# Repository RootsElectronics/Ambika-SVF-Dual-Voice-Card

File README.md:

# Ambika-SVF-Dual-Voice-Card
Adaptation of the Mutable Instruments Ambika SVF Voice Card in 0603 SMD, with 2 Voices per voice card

My initial prototype (verified working at 02/2021) utilised the original through hole zener diodes. On this version I have simply changed those for a surface mount equivalent. 

Will upload BOM soon, but for now:

There are a few of these out in the wild now, someone kindly noted a fix for calibration they were having on 2 out of their 3 voice cards.

To quote

"I swapped R10 and R32 to 36k and they all calibrated approximately in the middle of the range (it may be worth experimenting with the feedback cap as well I guess.... but I'm not going to !)"

Original design by émilie gillet

CC-BY-SA 3.0

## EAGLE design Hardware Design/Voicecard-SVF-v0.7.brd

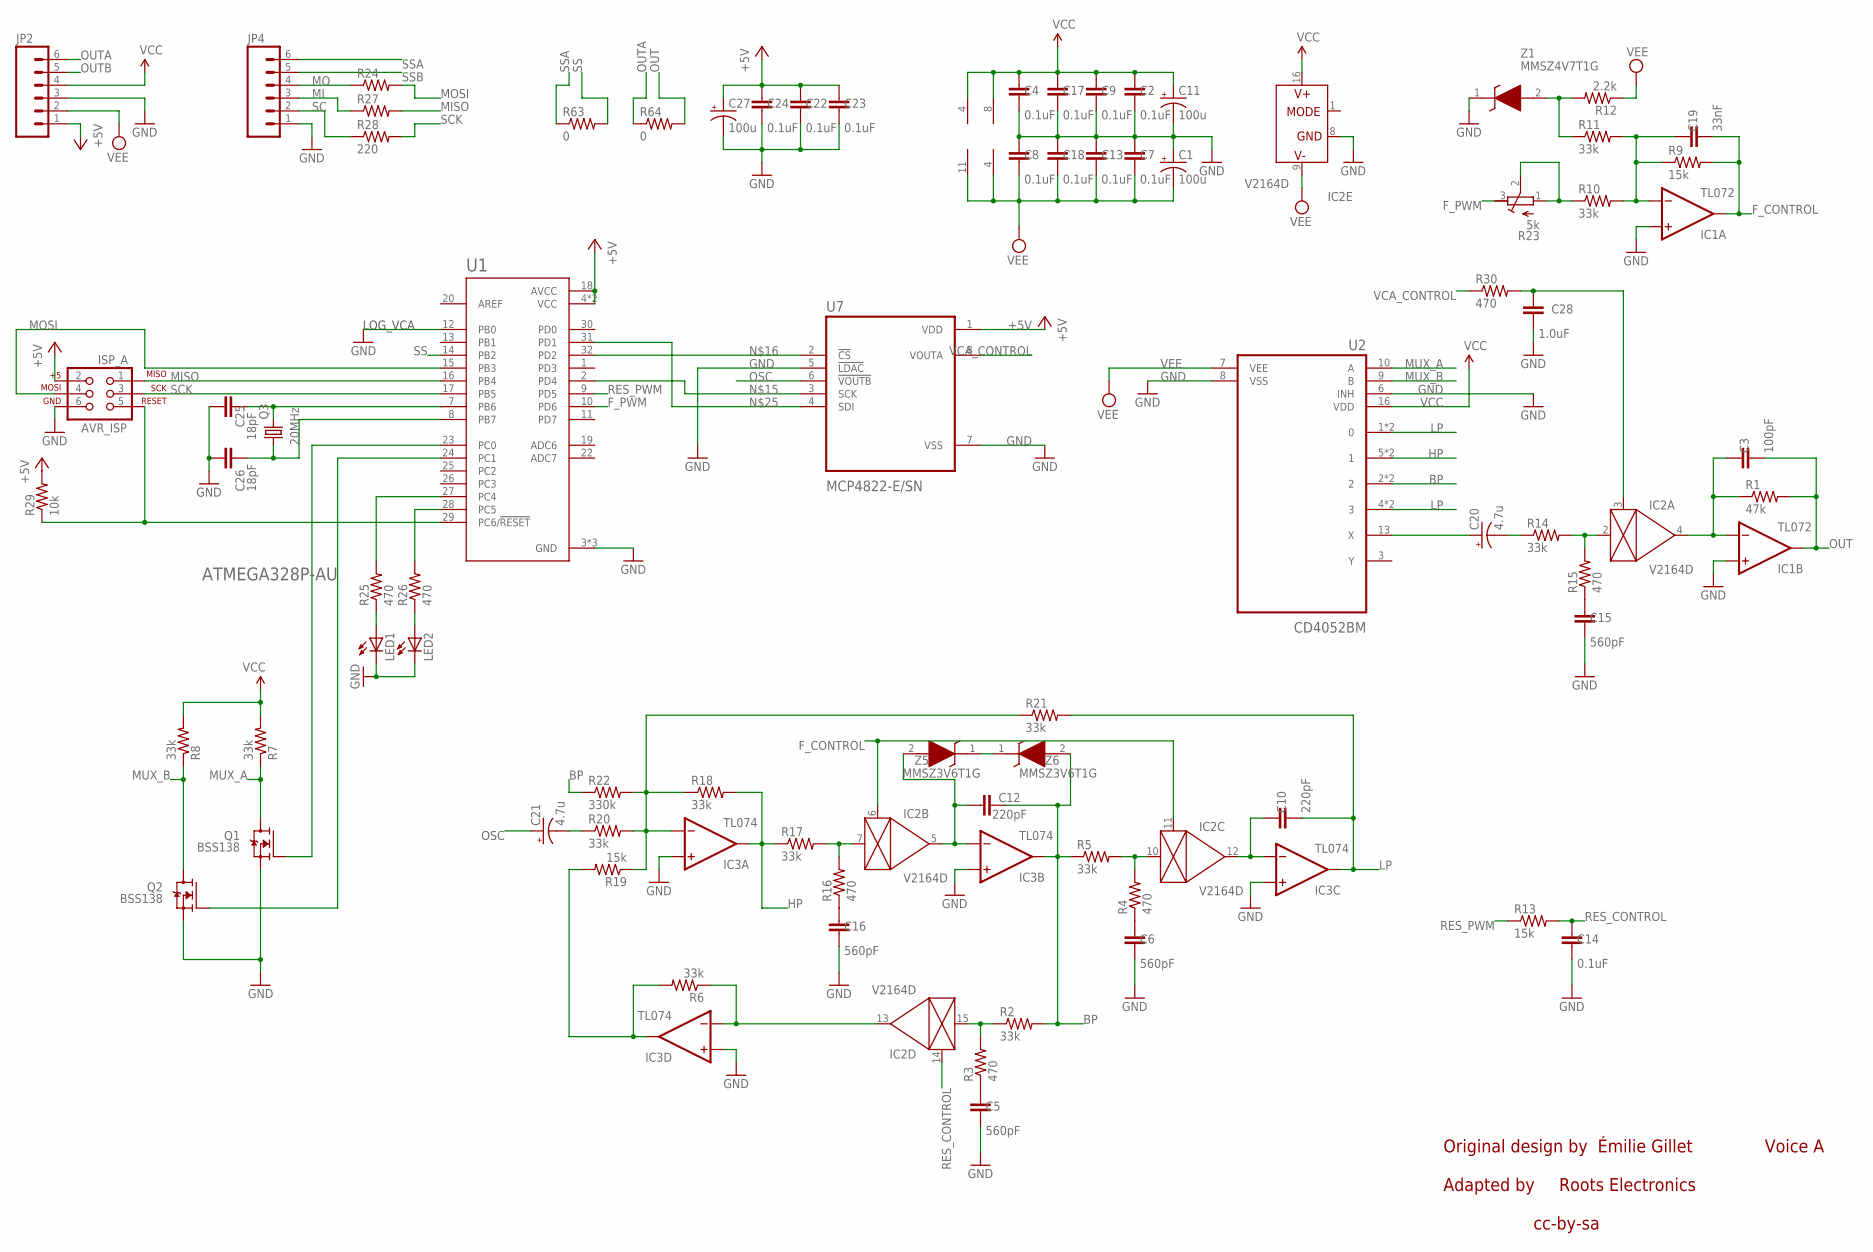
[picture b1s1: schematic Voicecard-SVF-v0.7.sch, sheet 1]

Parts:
C1, C11, C27: 100u; PANASONIC_C
C2, C4, C7, C8, C9, C13, C14, C17, C18, C22, C23, C24: 0.1uF; 0603
C3: 100pF; 0603
C5, C6, C15, C16: 560pF; 0603
C10, C12: 220pF; 0603
C19: 33nF; 0603
C20, C21: 4.7u; PANASONIC_A
C25, C26: 18pF; 0603
C28: 1.0uF; 0603
IC1: TL072; SO08
IC2: V2164D; SOIC16N
IC3: TL074; SO14
ISP_A: AVR_ISP; 2X3
JP2, JP4: M06SIP; 1X06
LED1, LED2: LED3MM
Q1, Q2: BSS138; SOT95P240X111-3N
Q3: 20MHz; HC49UP
R1: 47k; 0603
R2, R5, R6, R7, R8, R10, R11, R14, R17, R18, R20, R21: 33k; 0603
R3, R4, R15, R16, R25, R26, R30: 470; 0603
R9, R13, R19: 15k; 0603
R12: 2.2k; 0603
R22: 330k; 0603
R23: 5k; RTRIM3296P
R24, R27, R28: 220; 0603
R29: 10k; 0603
R63, R64: 0; 0603
U1: ATMEGA328P-AU; QFP80P900X900X120-32N
U2: CD4052BM; SOIC127P600X175-16N
U7: MCP4822-E/SN; SOIC127P599X175-8N
Z1: MMSZ4V7T1G; SOD3716X135N
Z5, Z6: MMSZ3V6T1G; SOD3716X135N

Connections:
+5V: C22.1, C23.1, C24.1, C27.+, ISP_A.2, JP2.1, R29.2, U1.4 (VCC), U1.6 (VCC), U1.18 (AVCC), U7.1 (VDD); also elsewhere on the board
BP: C12.2, IC3.7 (OUT), R2.2, R5.1, R22.1, U2.2, U2.15 (2), Z6.2 (A)
F_CONTROL: C19.2, IC1.1 (OUT), IC2.6 (CTRL), IC2.11 (CTRL), R9.2
F_PWM: R23.3 (A), U1.10 (PD6)
GND: C1.+, C2.2, C4.2, C5.2, C6.2, C7.1, C8.1, C9.2, C11.-, C13.1, C14.2, C15.2, C16.2, C17.2, C18.1, C22.2, C23.2, C24.2, C25.1, C26.1, C27.-, C28.2, IC1.3 (+IN), IC1.5 (+IN), IC2.8 (GND), IC3.3 (+IN), IC3.5 (+IN), IC3.10 (+IN), IC3.12 (+IN), ISP_A.6, JP2.3, JP4.1, LED1.K (C), LED2.K (C), Q1.2 (S), Q2.2 (S), U1.3 (GND), U1.5 (GND), U1.12 (PB0), U1.21 (GND), U2.6 (INH), U2.8 (VSS), U7.5 (!LDAC), U7.7 (VSS), Z1.1 (K); also elsewhere on the board
HP: IC3.1 (OUT), R17.1, R18.2, U2.5 (1), U2.14 (1)
LEDS0: R25.2, U1.27 (PC4)
LP: C10.2, IC3.8 (OUT), R21.2, U2.1 (0), U2.4 (3), U2.11 (3), U2.12 (0)
MI: JP4.3, R27.1; also elsewhere on the board
MISO: ISP_A.1, R27.2, U1.16 (PB4)
MO: JP4.4, R24.1; also elsewhere on the board
MOSI: ISP_A.4, R24.2, U1.15 (PB3)
MUX_A: Q1.3 (D), R7.1, U2.10 (A)
MUX_B: Q2.3 (D), R8.1, U2.9 (B)
unnamed: C21.-, R20.1
unnamed: C20.+, U2.13 (X)
unnamed: Q1.1 (G), U1.23 (PC0)
unnamed: C20.-, R14.1
unnamed: Q2.1 (G), U1.24 (PC1)
unnamed: LED1.A, R25.1
unnamed: R11.1, R12.2, Z1.2 (A)
unnamed: LED2.A, R26.1
unnamed: R26.2, U1.28 (PC5)
unnamed: IC3.2 (-IN), R18.1, R19.1, R20.2, R21.1, R22.2
unnamed: U1.2 (PD4), U7.3 (SCK)
unnamed: U1.32 (PD2), U7.2 (!CS)
unnamed: C6.1, R4.1
unnamed: C12.1, IC2.5 (OUT), IC3.6 (-IN), Z5.2 (A)
unnamed: IC2.15 (IN), R2.1, R3.2
unnamed: ISP_A.5, R29.1, U1.29 (PC6/!RESET)
unnamed: U1.31 (PD1), U7.4 (SDI)
unnamed: IC2.10 (IN), R4.2, R5.2
unnamed: C5.1, R3.1
unnamed: C10.1, IC2.12 (OUT), IC3.9 (-IN)
unnamed: IC2.7 (IN), R16.2, R17.2
unnamed: C16.1, R16.1
unnamed: IC2.13 (OUT), IC3.13 (-IN), R6.1
unnamed: C19.1, IC1.2 (-IN), R9.1, R10.2, R11.2
unnamed: R10.1, R23.1 (E), R23.2 (S)
unnamed: IC3.14 (OUT), R6.2, R19.2
unnamed: Z5.1 (K), Z6.1 (K)
unnamed: C15.1, R15.1
unnamed: IC2.2 (IN), R14.2, R15.2
unnamed: C3.1, IC1.6 (-IN), IC2.4 (OUT), R1.1
unnamed: C26.2, Q3.1, U1.8 (PB7)
unnamed: C25.2, Q3.2, U1.7 (PB6)
NET55: C28.1, IC2.3 (CTRL), R30.2
OSC: C21.+, U7.6 (!VOUTB)
OUT: C3.2, IC1.7 (OUT), R1.2, R64.2
OUTA: JP2.6, R64.1
OUTB: JP2.5; also elsewhere on the board
RES_CONTROL: C14.1, IC2.14 (CTRL), R13.2
RES_PWM: R13.1, U1.9 (PD5)
SC: JP4.2, R28.1; also elsewhere on the board
SCK: ISP_A.3, R28.2, U1.17 (PB5)
SS: R63.2, U1.14 (PB2)
SSA: JP4.6, R63.1
SSB: JP4.5; also elsewhere on the board
VCA_CONTROL: R30.1, U7.8 (VOUTA)
VCC: C2.1, C4.1, C9.1, C11.+, C17.1, IC1.8 (V+), IC2.16 (V+), IC3.4 (V+), JP2.4, R7.2, R8.2, U2.16 (VDD); also elsewhere on the board
VEE: C1.-, C7.2, C8.2, C13.2, C18.2, IC1.4 (V-), IC2.9 (V-), IC3.11 (V-), JP2.2, R12.1, U2.7 (VEE); also elsewhere on the board

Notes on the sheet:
Original design by
Émilie Gillet
LOG_VCA
Voice A
cc-by-sa
Adapted by
Roots Electronics

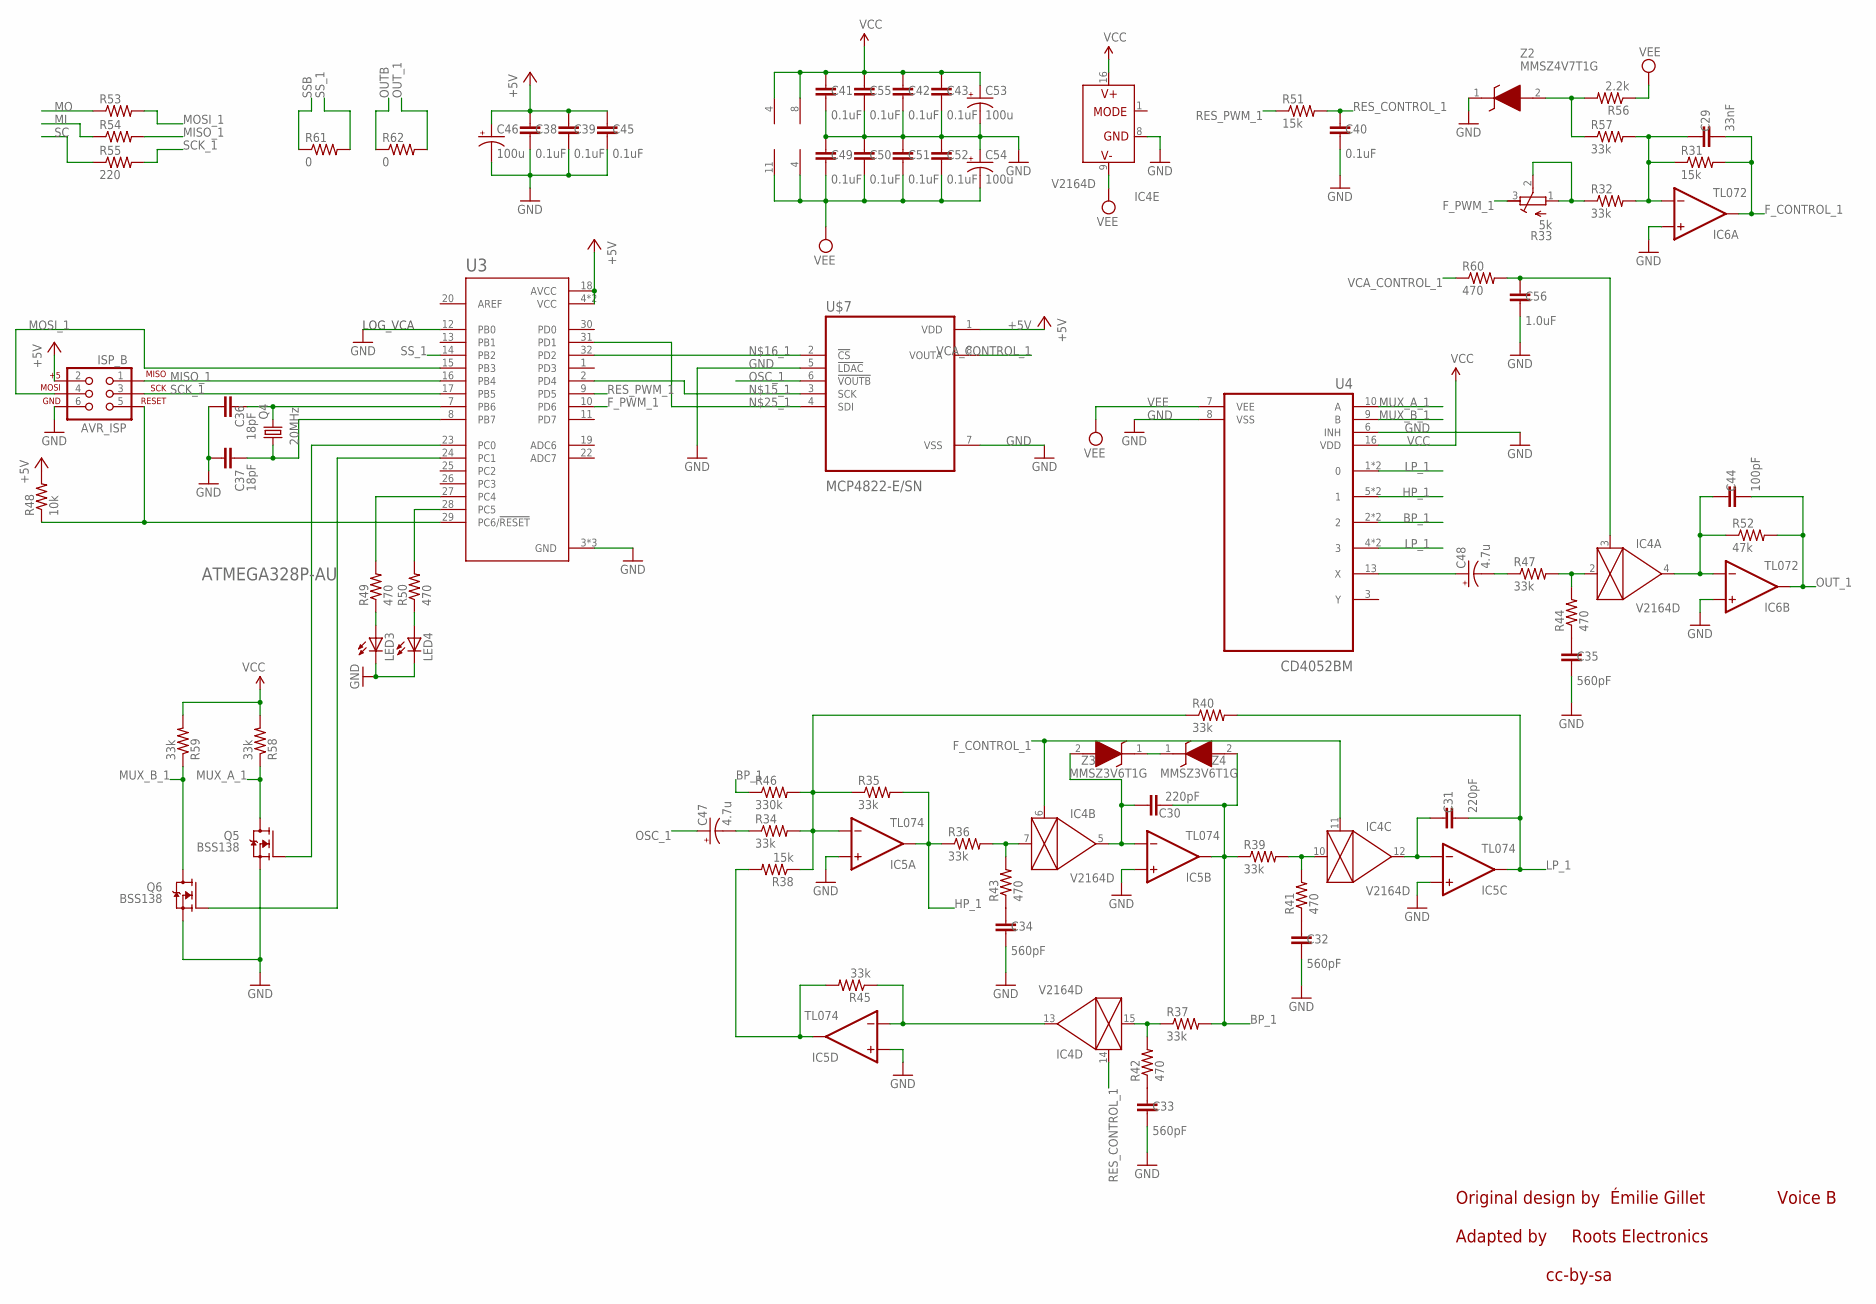
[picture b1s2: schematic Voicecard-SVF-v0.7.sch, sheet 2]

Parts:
C29: 33nF; 0603
C30, C31: 220pF; 0603
C32, C33, C34, C35: 560pF; 0603
C36, C37: 18pF; 0603
C38, C39, C40, C41, C42, C43, C45, C49, C50, C51, C52, C55: 0.1uF; 0603
C44: 100pF; 0603
C46, C53, C54: 100u; PANASONIC_C
C47, C48: 4.7u; PANASONIC_A
C56: 1.0uF; 0603
IC4: V2164D; SOIC16N
IC5: TL074; SO14
IC6: TL072; SO08
ISP_B: AVR_ISP; 2X3
LED3, LED4: LED3MM
Q4: 20MHz; HC49UP
Q5, Q6: BSS138; SOT95P240X111-3N
R31, R38, R51: 15k; 0603
R32, R34, R35, R36, R37, R39, R40, R45, R47, R57, R58, R59: 33k; 0603
R33: 5k; RTRIM3296P
R41, R42, R43, R44, R49, R50, R60: 470; 0603
R46: 330k; 0603
R48: 10k; 0603
R52: 47k; 0603
R53, R54, R55: 220; 0603
R56: 2.2k; 0603
R61, R62: 0; 0603
U3: ATMEGA328P-AU; QFP80P900X900X120-32N
U4: CD4052BM; SOIC127P600X175-16N
U$7: MCP4822-E/SN; SOIC127P599X175-8N
Z2: MMSZ4V7T1G; SOD3716X135N
Z3, Z4: MMSZ3V6T1G; SOD3716X135N

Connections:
+5V: C38.1, C39.1, C45.1, C46.+, ISP_B.2, R48.2, U3.4 (VCC), U3.6 (VCC), U3.18 (AVCC), U$7.1 (VDD); also elsewhere on the board
BP_1: C30.2, IC5.7 (OUT), R37.2, R39.1, R46.1, U4.2, U4.15 (2), Z4.2 (A)
F_CONTROL_1: C29.2, IC4.6 (CTRL), IC4.11 (CTRL), IC6.1 (OUT), R31.2
F_PWM_1: R33.3 (A), U3.10 (PD6)
GND: C32.2, C33.2, C34.2, C35.2, C36.1, C37.1, C38.2, C39.2, C40.2, C41.2, C42.2, C43.2, C45.2, C46.-, C49.1, C50.1, C51.1, C52.1, C53.-, C54.+, C55.2, C56.2, IC4.8 (GND), IC5.3 (+IN), IC5.5 (+IN), IC5.10 (+IN), IC5.12 (+IN), IC6.3 (+IN), IC6.5 (+IN), ISP_B.6, LED3.K (C), LED4.K (C), Q5.2 (S), Q6.2 (S), U3.3 (GND), U3.5 (GND), U3.12 (PB0), U3.21 (GND), U4.6 (INH), U4.8 (VSS), U$7.5 (!LDAC), U$7.7 (VSS), Z2.1 (K); also elsewhere on the board
HP_1: IC5.1 (OUT), R35.2, R36.1, U4.5 (1), U4.14 (1)
LEDS1_1: R49.2, U3.27 (PC4)
LP_1: C31.2, IC5.8 (OUT), R40.2, U4.1 (0), U4.4 (3), U4.11 (3), U4.12 (0)
MI: R54.1; also elsewhere on the board
MISO_1: ISP_B.1, R54.2, U3.16 (PB4)
MO: R53.1; also elsewhere on the board
MOSI_1: ISP_B.4, R53.2, U3.15 (PB3)
MUX_A_1: Q5.3 (D), R58.1, U4.10 (A)
MUX_B_1: Q6.3 (D), R59.1, U4.9 (B)
unnamed: C29.1, IC6.2 (-IN), R31.1, R32.2, R57.2
unnamed: R32.1, R33.1 (E), R33.2 (S)
unnamed: C44.1, IC4.4 (OUT), IC6.6 (-IN), R52.1
unnamed: IC5.2 (-IN), R34.2, R35.1, R38.1, R40.1, R46.2
unnamed: U3.2 (PD4), U$7.3 (SCK)
unnamed: U3.32 (PD2), U$7.2 (!CS)
unnamed: C30.1, IC4.5 (OUT), IC5.6 (-IN), Z3.2 (A)
unnamed: IC4.10 (IN), R39.2, R41.2
unnamed: C31.1, IC4.12 (OUT), IC5.9 (-IN)
unnamed: C32.1, R41.1
unnamed: U3.31 (PD1), U$7.4 (SDI)
unnamed: C33.1, R42.1
unnamed: IC4.7 (IN), R36.2, R43.2
unnamed: C34.1, R43.1
unnamed: C35.1, R44.1
unnamed: IC4.2 (IN), R44.2, R47.2
unnamed: IC4.15 (IN), R37.1, R42.2
unnamed: IC4.13 (OUT), IC5.13 (-IN), R45.1
unnamed: IC5.14 (OUT), R38.2, R45.2
unnamed: Z3.1 (K), Z4.1 (K)
unnamed: C47.-, R34.1
unnamed: C48.-, R47.1
unnamed: C37.2, Q4.1, U3.8 (PB7)
unnamed: C36.2, Q4.2, U3.7 (PB6)
unnamed: LED3.A, R49.1
unnamed: LED4.A, R50.1
unnamed: R50.2, U3.28 (PC5)
unnamed: R56.2, R57.1, Z2.2 (A)
unnamed: ISP_B.5, R48.1, U3.29 (PC6/!RESET)
unnamed: Q5.1 (G), U3.23 (PC0)
unnamed: Q6.1 (G), U3.24 (PC1)
unnamed: C48.+, U4.13 (X)
NET1: C56.1, IC4.3 (CTRL), R60.2
OSC_1: C47.+, U$7.6 (!VOUTB)
OUTB: R62.1; also elsewhere on the board
OUT_1: C44.2, IC6.7 (OUT), R52.2, R62.2
RES_CONTROL_1: C40.1, IC4.14 (CTRL), R51.2
RES_PWM_1: R51.1, U3.9 (PD5)
SC: R55.1; also elsewhere on the board
SCK_1: ISP_B.3, R55.2, U3.17 (PB5)
SSB: R61.1; also elsewhere on the board
SS_1: R61.2, U3.14 (PB2)
VCA_CONTROL_1: R60.1, U$7.8 (VOUTA)
VCC: C41.1, C42.1, C43.1, C53.+, C55.1, IC4.16 (V+), IC5.4 (V+), IC6.8 (V+), R58.2, R59.2, U4.16 (VDD); also elsewhere on the board
VEE: C49.2, C50.2, C51.2, C52.2, C54.-, IC4.9 (V-), IC5.11 (V-), IC6.4 (V-), R56.1, U4.7 (VEE); also elsewhere on the board

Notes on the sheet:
LOG_VCA
Voice B
Original design by
Émilie Gillet
cc-by-sa
Adapted by
Roots Electronics

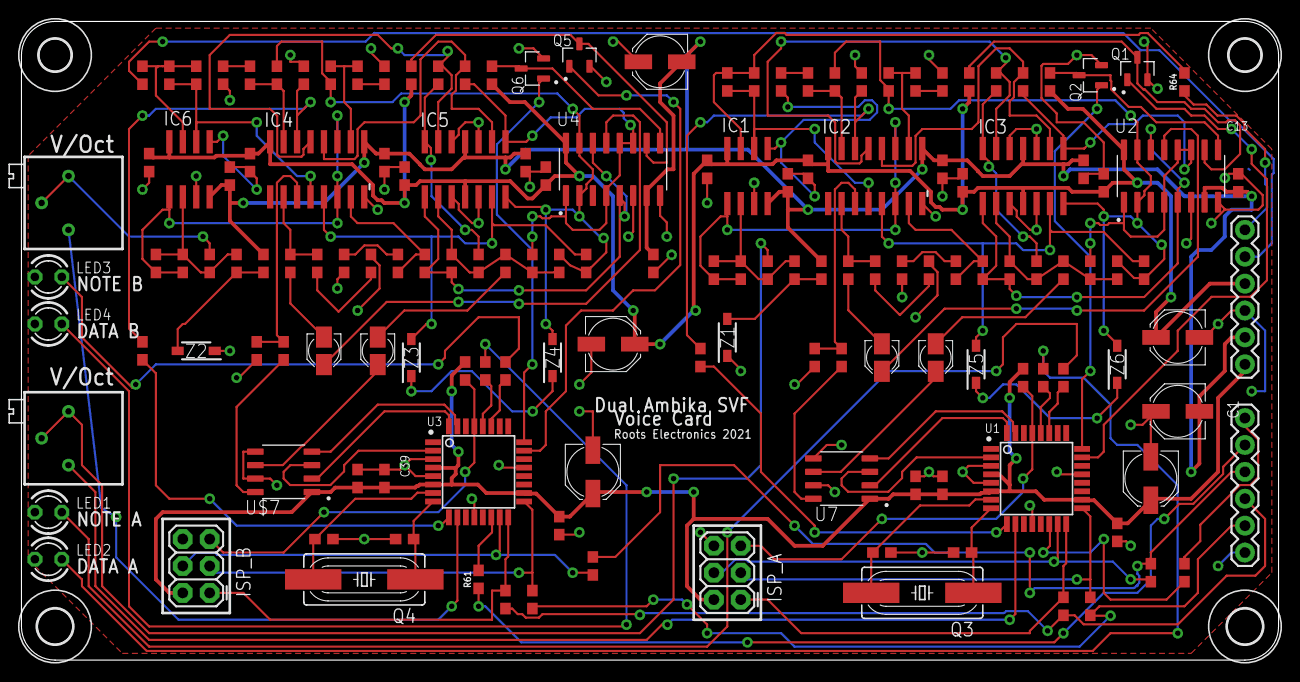
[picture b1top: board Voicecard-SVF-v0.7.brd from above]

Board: 2 copper layers, 118.7 x 60.3 mm, 156 parts (0 on the bottom side), 111 nets.

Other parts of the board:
U$1, U$2: 3,0
U$5, U$6: 3,3

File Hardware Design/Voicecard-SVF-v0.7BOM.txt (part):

Qty Value         Device                Package               Parts                                                                                                             Description                                                                             
4                 LED3MM                LED3MM                LED1, LED2, LED3, LED4                                                                                            LED                                                                                     
2                 M06SIP                1X06                  JP2, JP4                                                                                                          Header 6                                                                                
4   0             220OHM-0603-1/10W-1%  0603                  R61, R62, R63, R64                                                                                                220Ω resistor                                                                           
24  0.1uF         0.1UF-0603-25V-5%     0603                  C2, C4, C7, C8, C9, C13, C14, C17, C18, C22, C23, C24, C38, C39, C40, C41, C42, C43, C45, C49, C50, C51, C52, C55 0.1µF ceramic capacitors                                                                
2   1.0uF         1.0UF-0603-16V-10%    0603                  C28, C56                                                                                                          1µF ceramic capacitors                                                                  
2   100pF         100PF-0603-50V-5%     0603                  C3, C44                                                                                                           100pF/0.1nF ceramic capacitors                                                          
6   100u          CPOL-USC              PANASONIC_C           C1, C11, C27, C46, C53, C54                                                                                       POLARIZED CAPACITOR, American symbol                                                    
2   10k           10KOHM-0603-1/10W-1%  0603                  R29, R48                                                                                                          10kΩ resistor                                                                           
6   15k           15KOHM-0603-1/10W-1%  0603                  R9, R13, R19, R31, R38, R51                                                                                       15kΩ resistor                                                                           
4   18pF          18PF-0603-50V-5%      0603                  C25, C26, C36, C37                                                                                                18pF ceramic capacitors                                                                 
2   2.2k          2.2KOHM-0603-1/10W-1% 0603                  R12, R56                                                                                                          2.2kΩ resistor                                                                          
2   20MHz         CRYSTALHC49UP         HC49UP                Q3, Q4                                                                                                            CRYSTAL                                                                                 
6   220           220OHM-0603-1/10W-1%  0603                  R24, R27, R28, R53, R54, R55                                                                                      220Ω resistor                                                                           
4   220pF         270PF-0603-50V-5%     0603                  C10, C12, C30, C31                                                                                                270pF/0.27nF ceramic capacitors                                                         
2   330k          330KOHM-0603-1/10W-1% 0603                  R22, R46                                                                                                          330kΩ resistor                                                                          
24  33k           33KOHM-0603-1/10W-1%  0603                  R2, R5, R6, R7, R8, R10, R11, R14, R17, R18, R20, R21, R32, R34, R35, R36, R37, R39, R40, R45, R47, R57, R58, R59 33kΩ resistor                                                                           
2   33nF          33NF-0603-50V-10%     0603                  C19, C29                                                                                                          33nF ceramic capacitors                                                                 
4   4.7u          CPOL-USA              PANASONIC_A           C20, C21, C47, C48                                                                                                POLARIZED CAPACITOR, American symbol                                                    
14  470           470OHM-0603-1/10W-1%  0603                  R3, R4, R15, R16, R25, R26, R30, R41, R42, R43, R44, R49, R50, R60                                                470Ω resistor                                                                           
2   47k           47KOHM-0603-1/10W-1%  0603                  R1, R52                                                                                                           47kΩ resistor                                                                           
8   560pF         560PF-0603-50V-5%     0603                  C5, C6, C15, C16, C32, C33, C34, C35                                                                              0.56nF/560pF ceramic capacitors                                                         
2   5k            R-TRIMM3296P          RTRIM3296P            R23, R33                                                                                                          Trimm resistor                                                                          
2   ATMEGA328P-AU ATMEGA328P-AU         QFP80P900X900X120-32N U1, U3                                                                                                            ATmega Series 20 MHz 32 KB Flash 2 KB SRAM 8-Bit Microcontroller - TQFP-32 Check prices 
2   AVR_ISP       AVR_SPI_PRG_6PTH      2X3                   ISP_A, ISP_B                                                                                                      AVR ISP 6 Pin                                                                           
4   BSS138        BSS138                SOT95P240X111-3N      Q1, Q2, Q5, Q6                                                                                                    N-Channel 50V 220mA (Ta) 360mW (Ta) Surface Mount SOT-23-3  Check prices                
2   CD4052BM      CD4052BM              SOIC127P600X175-16N   U2, U4                                                                                                            Check prices                                                                            
2   MCP4822-E/SN  MCP4822-E/SN          SOIC127P599X175-8N    U$7, U7                                                                                                           Check prices                                                                            
4   MMSZ3V6T1G    MMSZ3V6T1G            SOD3716X135N          Z3, Z4, Z5, Z6                                                                                                    500 mW 3.6 V +/-5% ZenerDiodeVoltage Regulator                                          
2   MMSZ4V7T1G    MMSZ4V7T1G            SOD3716X135N          Z1, Z2                                                                                                            500 mW, 4.7 V +/-5% ZenerDiodeVoltage Regulator                                         
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

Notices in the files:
parts and their libraries:
SparkFun-Resistors: Licensing: Creative Commons ShareAlike 4.0 International - https://creativecommons.org/licenses/by-sa/4.0
